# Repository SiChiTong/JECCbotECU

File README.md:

# JECCbotECU

See Istrobot 2020 demo video of JECCbot mini with JECCbotECU solving task of RoboOrienteering (https://robotika.vosrk.cz/roboorienteering/index.php?year=2020&page=aktuality ): https://www.youtube.com/watch?v=Fceis1Gl848 .

This Repository contains everything about controlling the JECCbot mini ( https://github.com/generationmake/JECCbot_mini ) with a the JECCbotECU board. There is also included software with web frontend for a Raspberry Pi, to move the robot to GPS waypoints.

## Hardware

### PCB

The JECCbotECU is formed from the controller board ( data included in this repository ) and some motor driver stage ( tested with https://github.com/generationmake/HighPowerMotorFeatherWing/ ). The controller pcb in this repository features a Bosch BNO055 IMU, the connection of a KVH C100 compass unit, GPS and RPLidar, USB VCOMM, different voltage regulators, GPIO port and SW-Debugging.

### Case

There is also a case for the ECU unit with HighpowerMotorFeatherwing in this repository. It's size is 12cm x 10cm and it is fully compatible with the mountingholes on the JECCbot mini. On the top of the case, there is a snap in holder for a Einhell PowerXChange 18V drill battery.

## Software

### ECU 
 
The ECU Software is written in C using the STM32 Cube HAL hardware abstraction layer. It currently features control of two dc motors, emergency stop, rplidar, gps and compass decoding and driving the robot along a heading to north.

Here You can see the configured pinout of the STM32F103C8T6 mikrocontroller, which is compatible to STM32 Bluepill evalboard:

#### Computer interaction

The ECU can interact with computer by using USB and a state based api.

##### Description of implemented states

###### State 0 - Joydrive

The direction and speed of the motors can be manipulated with the registers ```PWM_LEFT``` and ```PWM_RIGHT```. The value ranges are int16.

###### State 1 - Drive along compass heading

The robot can drive along a heading from -180° to 180° saved in the ```MOVEHEADING_HEADING``` register with a int16 speed in ```MOVEHEADING_SPEED``` by using a P-Controller with the parameter register ```MOVEHEADING_P```.

#### Protocol

The protocol is leaned on ASCII-Modbus and is register based. 

Every protocol instruction message begins with ```:```, which is followed with a 8 bit instructor. Then there is a 16 bit hex register address and a 16 bit or 32 bit hex register value ( interpreted as signed int ). Every message ends with ```\n```: 

```:<instructor><hex address><hex value>\n```

The mikrocontroller answers with ```:```, the register, value and ```\n```;

###### Protocol Configuration

```
API_MEMORY_SIZE 400

API_STATE_JOYDRIVE 0x0000
API_STATE_MOVEHEADING 0x0001

API_INSTRUCTION_READ 0x02
API_INSTRUCTION_WRITE 0x04

API_ERROR_WRONG_FORMAT 0x0000
API_ERROR_INVALID_ADDRESS 0x0001
API_ERROR_WRONG_INSTRUCTOR 0x0002
API_ERROR_ACCESS_DENIED 0x0003

API_REG_STATE 0x0000

API_REG_PWMLEFT 0x0002
API_REG_PWMRIGHT 0x0004

API_REG_MOVEHEADING_P 0x0005
API_REG_MOVEHEADING_SPEED 0x0006
API_REG_MOVEHEADING_HEADING 0x0007

API_BENCH_LIDAR_START 0x000f
API_BENCH_LIDAR_END API_BENCH_LIDAR_START + 360

API_REG_HEADING_KVH 0x0178

API_BENCH_GPS_START 0x0179
API_BENCH_GPS_END API_BENCH_GPS_START + 5
```

###### Example

Set robot state to 1:

Instruction: ```:04000000001\n``` -> Response ```:00000001\n```.

###### Error Codes

Every error code starts with the command e and has a specific index ( %03d ) as parameter, e. g. ```:e001\n```.

| Index | Meaning |
| ----- | ------- |
| 000 | received data is no command |
| 001 | Command is not found |
| 002 | Syntax error in command |

#### KVH Terminal

There is also a program included that lets the ECU act as a terminal to a connected KVH C100 compass unit. This can be used for calibrating the compass.

### Raspberry Pi

The main sotware used in the demonstration for Istrobot 2020 ( https://www.youtube.com/watch?v=Fceis1Gl848 ) is also included as a Codeblocks project.
In the html folder You can find the frontend design with commands to the robot via HTTP POST.

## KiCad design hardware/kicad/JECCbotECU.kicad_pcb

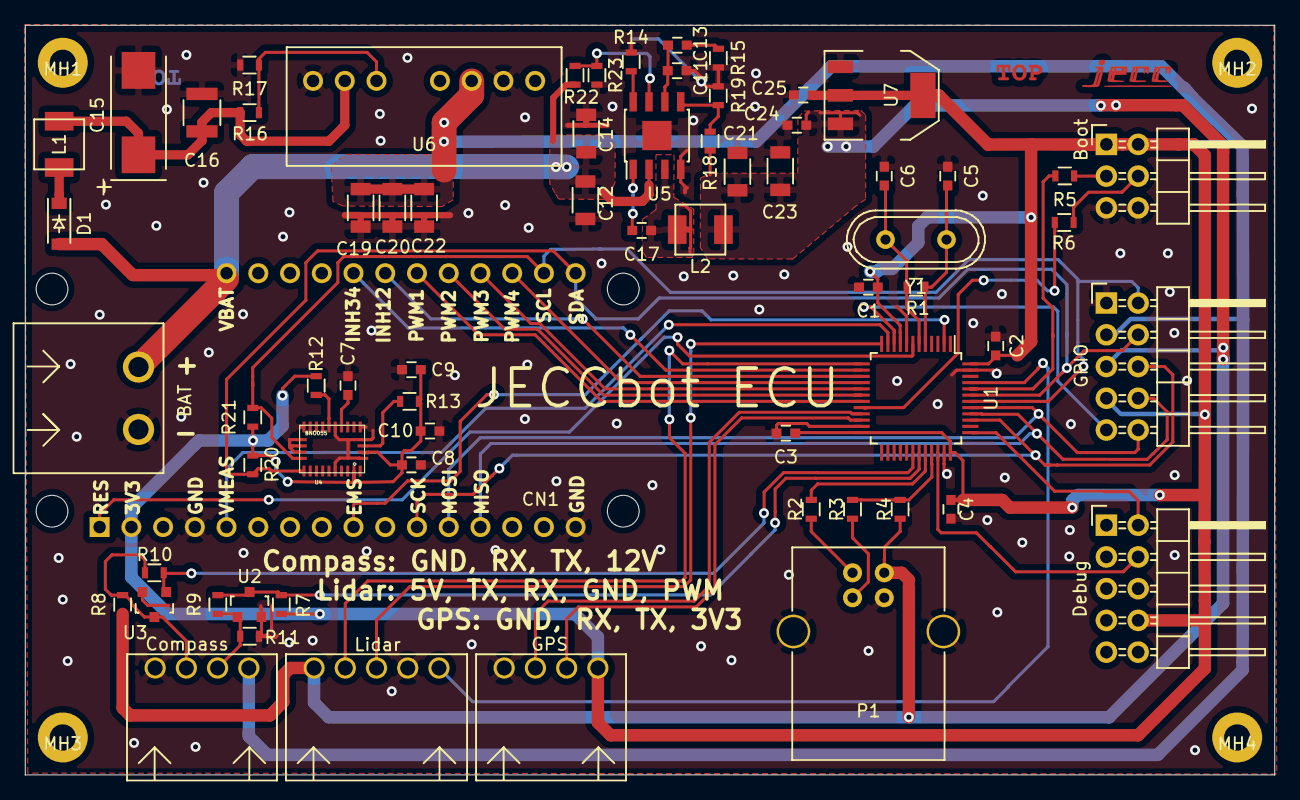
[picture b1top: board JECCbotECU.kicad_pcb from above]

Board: 2 copper layers, 100.0 x 60.0 mm, 71 parts (0 on the bottom side), 54 nets.

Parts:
BAT: WR-TBL_691313710002
Boot: CONN_02X03; Pin_Header_Angled_2x03
C1, C2, C3, C4, C7, C9: 100nF; C_0603
C5, C6: 20pF; C_0603
C8: 6.8nF; C_0603
C10: 120nF; C_0603
C11: 120p; C_0603
C12, C14: C_1206
C13: 12n; C_0603
C15: Tanal D; TantalC_SizeD_EIA-7343_Wave
C16: 4.7uF 50V; C_1210
C17: 100n; C_0603
C19, C20, C22: 22uF; C_1206
C21, C23: 22u; C_1206
C24: 10uF; C_0603
C25: 22uF; C_0603
CN1: ADAFRUIT_FEATHER; ADAFRUIT_FEATHER_HOLES
Compass: 691382010004; WR-TBL_691382010004
D1: D_Small; SOD-123
Debug: CONN_02X05; Pin_Header_Angled_2x05
GPIO: CONN_02X05; Pin_Header_Angled_2x05
GPS: 691382010004; WR-TBL_691382010004
L1: WE-LHMI40xx
L2: WE-74437324150; WE-LHMI40xx
Lidar: 691382010005; WR-TBL_691382010005
MH1, MH2, MH3, MH4: MH_210_400_NP
P1: USB_B
R1: 1M; R_0603
R2, R3: 20; R_0603
R4: 4.7k; R_0603
R5, R6, R18: 100k; R_0603
R7, R8: 1k; R_0603
R9, R10, R16, R17: DNI; R_0603
R11, R12, R13, R20, R21: 10k; R_0603
R14: 143k; R_0603
R15: 3.74k; R_0603
R19: 19.1k; R_0603
R22: 220k; R_0603
R23: 43.2k; R_0603
U1: STM32F103C8Tx; LQFP-48_7x7mm_Pitch0.5mm
U2, U3: BSS138; SOT-23
U4: BNO055; LGA-28-5832
U5: TPS54335A; SOIC-8-1EP_3.9x4.9mm_Pitch1.27mm
U6: GAPTEC_6S8W4_1.6RP
U7: LT1117; SOT-223
Y1: Crystal_Small; Crystal_HC49-U_Vertical

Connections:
+3V3: Boot.1, Boot.2, C1.1, C2.1, C3.1, C4.1, C8.2, C9.1, C10.1, C25.1, CN1.2, Debug.8, GPIO.7, GPS.4, R7.1, R12.1, R13.1, R20.1, R21.1, U1.9, U1.24, U1.36, U1.48, U4.3, U4.28, U7.2, U7.4
+5V: C21.1, C23.1, C24.1, GPIO.5, L2.2, Lidar.1, P1.1, R4.2, R8.1, R18.1, U7.3
+12V: C19.1, C20.1, C22.1, Compass.4, GPIO.3, U6.6
/power/REG_5V_BOOT: C17.2, U5.1
/power/REG_5V_COMP: C11.1, C13.1, U5.6
/power/REG_5V_COMP_C: C13.2, R15.1
/power/REG_5V_PH: C17.1, L2.1, U5.3
/power/REG_5V_RT: R14.1, U5.8
/power/REG_5V_SENSE: R18.2, R19.1, U5.5
/power/VIN: C15.1, C16.1, L1.2, R16.1, U6.2
/power/VIN_D: D1.1, L1.1
BOOT0: R5.2, U1.44
BOOT1: R6.1, U1.20
EM_STOP_D: CN1.9, U1.2
GND: Boot.5, Boot.6, C1.2, C2.2, C3.2, C4.2, C5.1, C6.1, C7.2, C8.1, C9.2, C10.2, C11.2, C12.2, C14.2, C15.2, C16.2, C19.2, C20.2, C21.2, C22.2, C23.2, C24.2, C25.2, CN1.4, CN1.16, Compass.1, Debug.6, GPIO.1, GPS.1, Lidar.4, P1.4, P1.5, R11.2, R14.2, R15.2, R17.2, R19.2, R23.2, U1.8, U1.23, U1.35, U1.47, U2.2, U3.2, U4.2, U4.5, U4.6, U4.10, U4.15, U4.16, U4.17, U4.18, U4.25, U5.4, U5.9, U6.1, U6.7, U7.1
GPIO: GPIO.9, U1.10
GPS_RX: GPS.3, U1.22
GPS_TX: GPS.2, U1.21
I2C_SCL: CN1.18, GPIO.2, R21.2, U1.42, U4.19
I2C_SDA: CN1.17, GPIO.4, R20.2, U1.43, U4.20
INH12: CN1.23, U1.15
INH34: CN1.24, U1.14
KVH_RX: R7.2, R9.2, U1.31, U2.3
KVH_TX: R10.1, U1.30, U3.1
LIDAR_PWM: Lidar.5, U1.45
LIDAR_RX: Lidar.2, U1.13
LIDAR_TX: Lidar.3, U1.12
unnamed: Boot.3, R5.1
unnamed: Boot.4, R6.2
unnamed: C7.1, U4.9
unnamed: Compass.2, R8.2, R10.2, U3.3
unnamed: Compass.3, R9.1, R11.1, U2.1
unnamed: P1.2, R2.2
unnamed: P1.3, R3.1
unnamed: R12.2, U4.11
unnamed: R13.2, U4.4
unnamed: R16.2, R17.1, U6.3
unnamed: R22.2, R23.1, U5.7
OSC_IN: C5.2, R1.2, U1.5, Y1.1
OSC_OUT: C6.2, R1.1, U1.6, Y1.2
PWM1: CN1.22, U1.19
PWM2: CN1.21, U1.18
PWM3: CN1.20, U1.17
PWM4: CN1.19, U1.16
RESET: CN1.1, U1.7
SPI_MISO: CN1.13, GPIO.8, U1.40
SPI_MOSI: CN1.12, GPIO.10, U1.41
SPI_SCK: CN1.11, GPIO.6, U1.39
SWCLK: Debug.2, U1.37
SWDIO: Debug.4, U1.34
USB+: R3.2, R4.1, U1.33
USB-: R2.1, U1.32
VBAT: BAT.1, C12.1, C14.1, CN1.28, D1.2, R22.1, U5.2
VIN_MEAS: CN1.5, U1.11

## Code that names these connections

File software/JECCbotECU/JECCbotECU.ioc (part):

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Mcu.Name=STM32F103C(8-B)Tx
Mcu.Package=LQFP48
Mcu.UserName=STM32F103C8Tx
PA10.GPIOParameters=GPIO_Label
PA10.GPIO_Label=KVH_RX
PA10.Mode=Asynchronous
PA10.Signal=USART1_RX
PA11.Mode=Device
PA11.Signal=USB_DM
PA12.Mode=Device
PA12.Signal=USB_DP
PA13.Mode=Serial_Wire
PA13.Signal=SYS_JTMS-SWDIO
PA14.Mode=Serial_Wire
PA14.Signal=SYS_JTCK-SWCLK
PA2.GPIOParameters=GPIO_Label
PA2.GPIO_Label=LIDAR_TX
PA2.Mode=Asynchronous
PA2.Signal=USART2_TX
PA3.GPIOParameters=GPIO_Label
PA3.GPIO_Label=LIDAR_RX
PA3.Mode=Asynchronous
PA3.Signal=USART2_RX
PA4.GPIOParameters=GPIO_Label
PA4.GPIO_Label=INH34
PA4.Signal=GPIO_Output
PA5.GPIOParameters=GPIO_Label
PA5.GPIO_Label=INH12
PA5.Signal=GPIO_Output
PA6.GPIOParameters=GPIO_Label
PA6.GPIO_Label=PWM4
PA6.Signal=S_TIM3_CH1
PA7.GPIOParameters=GPIO_Label
PA7.GPIO_Label=PWM3
PA7.Signal=S_TIM3_CH2
PA9.GPIOParameters=GPIO_Label
PA9.GPIO_Label=KVH_TX
PA9.Mode=Asynchronous
PA9.Signal=USART1_TX
PB0.GPIOParameters=GPIO_Label
PB0.GPIO_Label=PWM2
PB0.Signal=S_TIM3_CH3
PB1.GPIOParameters=GPIO_Label
PB1.GPIO_Label=PWM1
PB1.Signal=S_TIM3_CH4
PB10.GPIOParameters=GPIO_Label
PB10.GPIO_Label=GPS_TX
PB10.Mode=Asynchronous
PB10.Signal=USART3_TX
PB11.GPIOParameters=GPIO_Label
PB11.GPIO_Label=GPS_RX
PB11.Mode=Asynchronous
PB11.Signal=USART3_RX
PB6.Mode=I2C
PB6.Signal=I2C1_SCL
PB7.Mode=I2C
PB7.Signal=I2C1_SDA
PB8.GPIOParameters=GPIO_Label
PB8.GPIO_Label=LIDAR_PWM
PB8.Signal=S_TIM4_CH3
PC13-TAMPER-RTC.GPIOParameters=PinState,GPIO_Label
PC13-TAMPER-RTC.GPIO_Label=LED_ONBOARD
PC13-TAMPER-RTC.PinState=GPIO_PIN_SET
PC13-TAMPER-RTC.Signal=GPIO_Output
PD0-OSC_IN.Mode=HSE-External-Oscillator
PD0-OSC_IN.Signal=RCC_OSC_IN
PD1-OSC_OUT.Mode=HSE-External-Oscillator
PD1-OSC_OUT.Signal=RCC_OSC_OUT
RCC.SYSCLKFreq_VALUE=72000000
RCC.SYSCLKSource=RCC_SYSCLKSOURCE_PLLCLK
board=custom

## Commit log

2020-04-03 added software project
2020-04-04 added kicad source
2020-04-04 changed directory
2020-04-04 added schematics pdf
2020-04-04 bugfix
2020-04-05 finished schematics
2020-04-05 started pcb
2020-04-05 component placement almost done
2020-04-05 pcb placement
2020-04-05 finished component placement
2020-04-13 finished layout
2020-04-13 removed bak
2020-04-13 layout 2.0
2020-04-14 silkscreen design
2020-04-14 added silkscreen pinouts
2020-04-14 improved ground
2020-04-15 updated schematics
2020-04-15 moved top label
2020-04-15 renamed
2020-04-15 added step
2020-04-16 design rules check
2020-04-16 improved layout
2020-04-16 checked overlay with motordriver board
2020-04-16 updated software
2020-04-16 fixed gps bug
2020-04-17 implemented gps encoding and added safe write/ read functions to api
2020-04-19 fixed nvix ;-(
2020-04-19 hopefully working function
2020-04-28 fixed layout and created case
2020-04-28 added list of power pcbs
2020-04-28 added spacers
2020-05-11 added gcode for case
2020-05-11 implemented compass and gps to api decoding
2020-05-11 added terminal program for kvh compass
2020-05-11 added more efficient data processing
2020-05-12 added control routine for moving along heading
2020-05-16 added raspberry pi codeblocks project
2020-05-16 added rendering
2020-05-16 added complete unit
2020-05-16 added case view
2020-05-16 added webpage
2020-05-16 added pinout
2020-05-17 updated ECU software
